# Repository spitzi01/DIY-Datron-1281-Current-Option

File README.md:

# DIY-Datron-1281-Current-Option
Add current measurement capabilities to your Datron 1281

I bought a defective Datron 1281. Sadly there was no option installed. So replicated the current measurement board as closely as I could. Most of the parts are still avaiable. The CLA3106 ASIC can be replaced with my CPLD replacement. The only problems are the JFETs for switching the low current ranges and the shunt resistors. The original JFETs were replaced with similar off-the-shelf ones. The shunt resistors are the most expensive part of this project, but there is no real other choice than Vishay foil resistors. Some resistors are custom ordered from Texas Components. The PCB features full mechanical compatibility to the original board and all guard traces.

I did some noise and linearity measurements with a DIY multifunction calibrator which uses a AD5791B and a ADR1000. The visible INL is due to the DAC INL. The noise of the 100mA range for example is 0,5µA pk2pk and 0,12µA rms. It is very possible that these measurements describe the performance of the calibrator. To know for sure, I would need a known current source.

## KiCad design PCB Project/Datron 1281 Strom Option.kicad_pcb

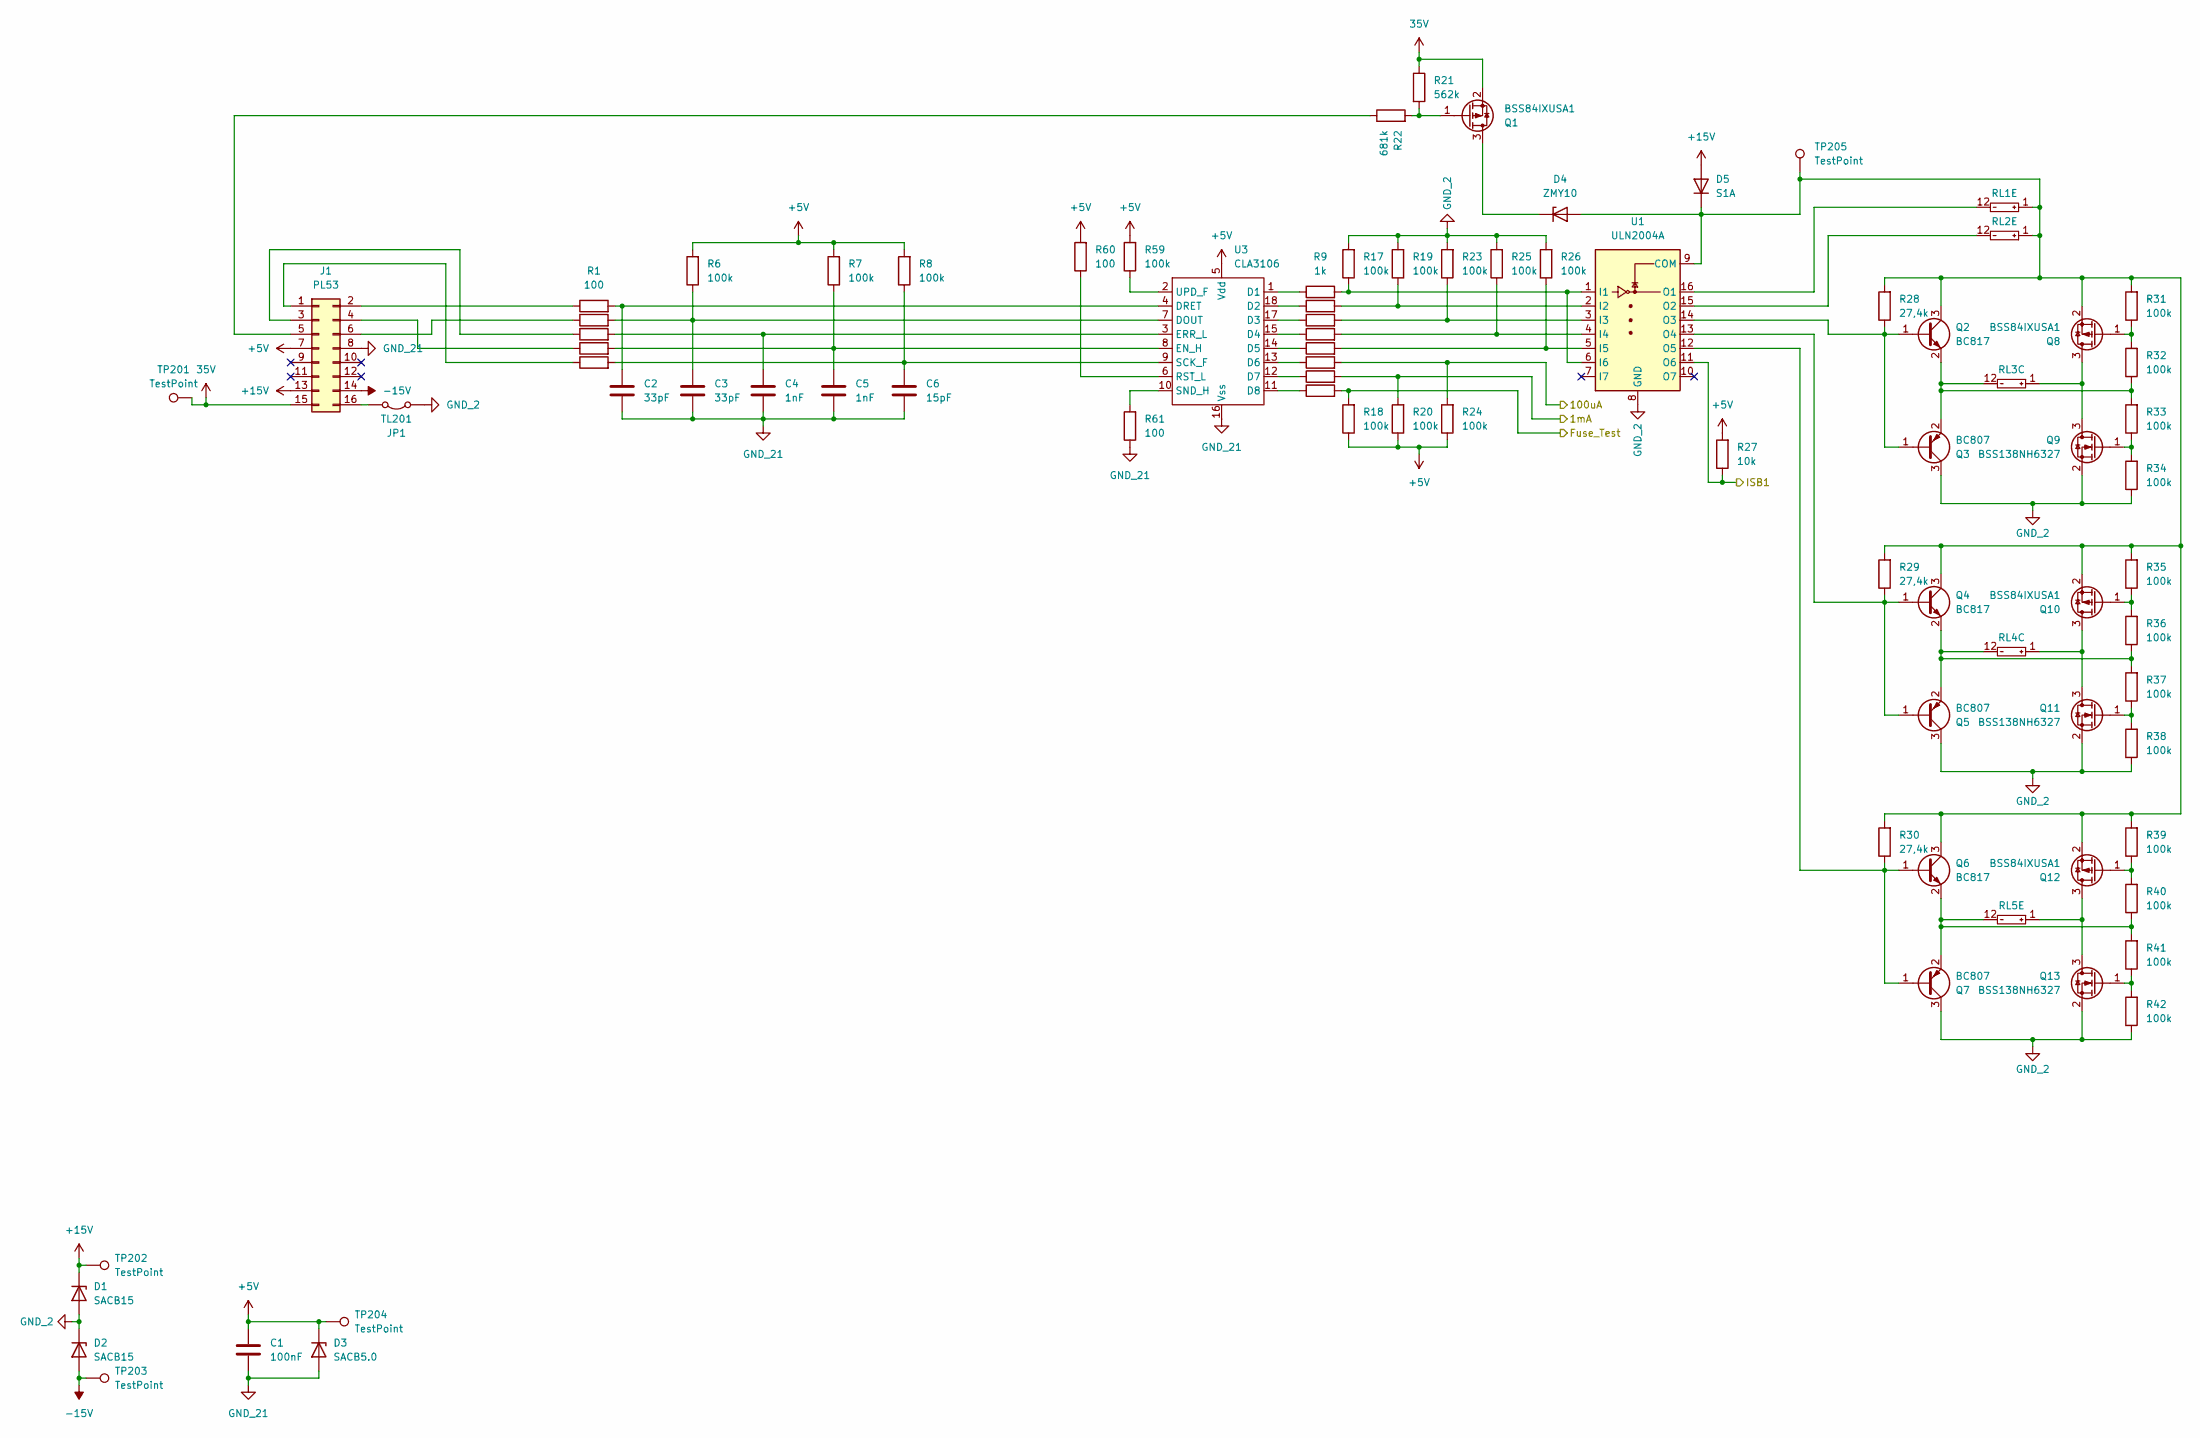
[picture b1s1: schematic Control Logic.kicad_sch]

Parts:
C1: 100nF; C_0805_2012Metric
C2, C3: 33pF; C_0805_2012Metric
C4, C5: 1nF; C_0805_2012Metric
C6: 15pF; C_0805_2012Metric
D1, D2: SACB15; D_SMB
D3: SACB5.0; D_SMB
D4: ZMY10; D_MELF
D5: S1A; D_SMA
J1: PL53; IDC-Header_2x08_P2.54mm_Vertical
JP1: TL201; TestPoint_2Pads_Pitch5.08mm_Drill1.3mm
Q1, Q8, Q10, Q12: BSS84IXUSA1; SOT-23-3
Q2, Q4, Q6: BC817; SOT-23
Q3, Q5, Q7: BC807; SOT-23
Q9, Q11, Q13: BSS138NH6327; SOT-23-3
R1, R2, R3, R4, R5, R60, R61: 100; R_0805_2012Metric
R6, R7, R8, R17, R18, R19, R20, R23, R24, R25, R26, R31, R32, R33, R34, R35, R36, R37, R38, R39, R40, R41, R42, R59: 100k; R_0805_2012Metric
R9, R10, R11, R12, R13, R14, R15, R16: 1k; R_0805_2012Metric
R21: 562k; R_0805_2012Metric
R22: 681k; R_0805_2012Metric
R27: 10k; R_0805_2012Metric
R28, R29, R30: 27,4k; R_0805_2012Metric
RL1, RL5: S3-DC24V; S3DC24V; Manufacturer_Part_Number S3-DC24V
RL2: S2-DC24V; S3DC24V; Manufacturer_Part_Number S2-DC24V
RL3, RL4: TX2-24V; Mouser Part Number 769-TX2-24V
TP201, TP202, TP203, TP204, TP205: TestPoint; TestPoint_Loop_D2.50mm_Drill1.0mm
U1: ULN2004A; SOIC-16W_5.3x10.2mm_P1.27mm
U3: CLA3106; DIP-18_W7.62mm_LongPads

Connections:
35V: J1.15, Q1.2 (S), R21.1, TP201.1
+5V: C1.1, D3.1 (K), J1.7, R6.2, R7.2, R8.2, R18.1, R20.1, R24.1, R27.2, R59.2, R60.2, TP204.1, U3.5 (Vdd); also elsewhere on the board
+15V: D1.1 (K), D5.2 (A), J1.13, TP202.1; also elsewhere on the board
-15V: D2.2 (A), J1.14, TP203.1; also elsewhere on the board
/Control Logic/1mA: R15.2, R20.2; also elsewhere on the board
/Control Logic/100uA: R14.2, R24.2; also elsewhere on the board
/Control Logic/Fuse_Test: R16.2, R18.2; also elsewhere on the board
/Control Logic/ISB1: R27.1, U1.11 (O6); also elsewhere on the board
GND_2: D1.2 (A), D2.1 (K), JP1.1 (A), Q3.3 (C), Q5.3 (C), Q7.3 (C), Q9.2 (S), Q11.2 (S), Q13.2 (S), R17.2, R19.2, R23.2, R25.2, R26.2, R34.1, R38.1, R42.1, U1.8 (GND); also elsewhere on the board
GND_21: C1.2, C2.2, C3.2, C4.2, C5.2, C6.2, D3.2 (A), J1.8, R61.1, U3.16 (Vss); also elsewhere on the board
unnamed: D4.2 (A), D5.1 (K), Q2.3 (C), Q4.3 (C), Q6.3 (C), Q8.2 (S), Q10.2 (S), Q12.2 (S), R28.2, R29.2, R30.2, R31.2, R35.2, R39.2, RL1.1, RL2.1, TP205.1, U1.9 (COM)
unnamed: D4.1 (K), Q1.3 (D)
unnamed: J1.1, R5.1
unnamed: J1.2, R1.1
unnamed: J1.3, R3.1
unnamed: J1.4, R4.1
unnamed: J1.5, R22.1
unnamed: J1.6, R2.1
unnamed: J1.16, JP1.2 (B)
unnamed: Q1.1 (G), R21.2, R22.2
unnamed: Q2.1 (B), Q3.1 (B), R28.1, U1.14 (O3)
unnamed: Q2.2 (E), Q3.2 (E), R32.1, R33.2, RL3.12
unnamed: Q4.1 (B), Q5.1 (B), R29.1, U1.13 (O4)
unnamed: Q4.2 (E), Q5.2 (E), R36.1, R37.2, RL4.12
unnamed: Q6.1 (B), Q7.1 (B), R30.1, U1.12 (O5)
unnamed: Q6.2 (E), Q7.2 (E), R40.1, R41.2, RL5.12
unnamed: Q8.3 (D), Q9.3 (D), RL3.1
unnamed: Q8.1 (G), R31.1, R32.2
unnamed: Q9.1 (G), R33.1, R34.2
unnamed: Q10.3 (D), Q11.3 (D), RL4.1
unnamed: Q10.1 (G), R35.1, R36.2
unnamed: Q11.1 (G), R37.1, R38.2
unnamed: Q12.3 (D), Q13.3 (D), RL5.1
unnamed: Q12.1 (G), R39.1, R40.2
unnamed: Q13.1 (G), R41.1, R42.2
unnamed: R9.2, R17.1, U1.1 (I1), U1.6 (I6)
unnamed: R10.2, R19.1, U1.2 (I2)
unnamed: R11.2, R23.1, U1.3 (I3)
unnamed: R12.2, R25.1, U1.4 (I4)
unnamed: R13.2, R26.1, U1.5 (I5)
unnamed: RL1.12, U1.16 (O1)
unnamed: RL2.12, U1.15 (O2)
unnamed: R9.1, U3.1 (D1)
unnamed: R10.1, U3.18 (D2)
unnamed: R11.1, U3.17 (D3)
unnamed: R12.1, U3.15 (D4)
unnamed: R13.1, U3.14 (D5)
unnamed: R14.1, U3.13 (D6)
unnamed: R15.1, U3.12 (D7)
unnamed: R16.1, U3.11 (D8)
unnamed: C3.1, R2.2, R6.1, U3.7 (DOUT)
unnamed: C2.1, R1.2, U3.4 (DRET)
unnamed: C5.1, R4.2, R7.1, U3.8 (EN_H)
unnamed: C4.1, R3.2, U3.3 (ERR_L)
unnamed: R60.1, U3.6 (RST_L)
unnamed: C6.1, R5.2, R8.1, U3.9 (SCK_F)
unnamed: R61.2, U3.10 (SND_H)
unnamed: R59.1, U3.2 (UPD_F)

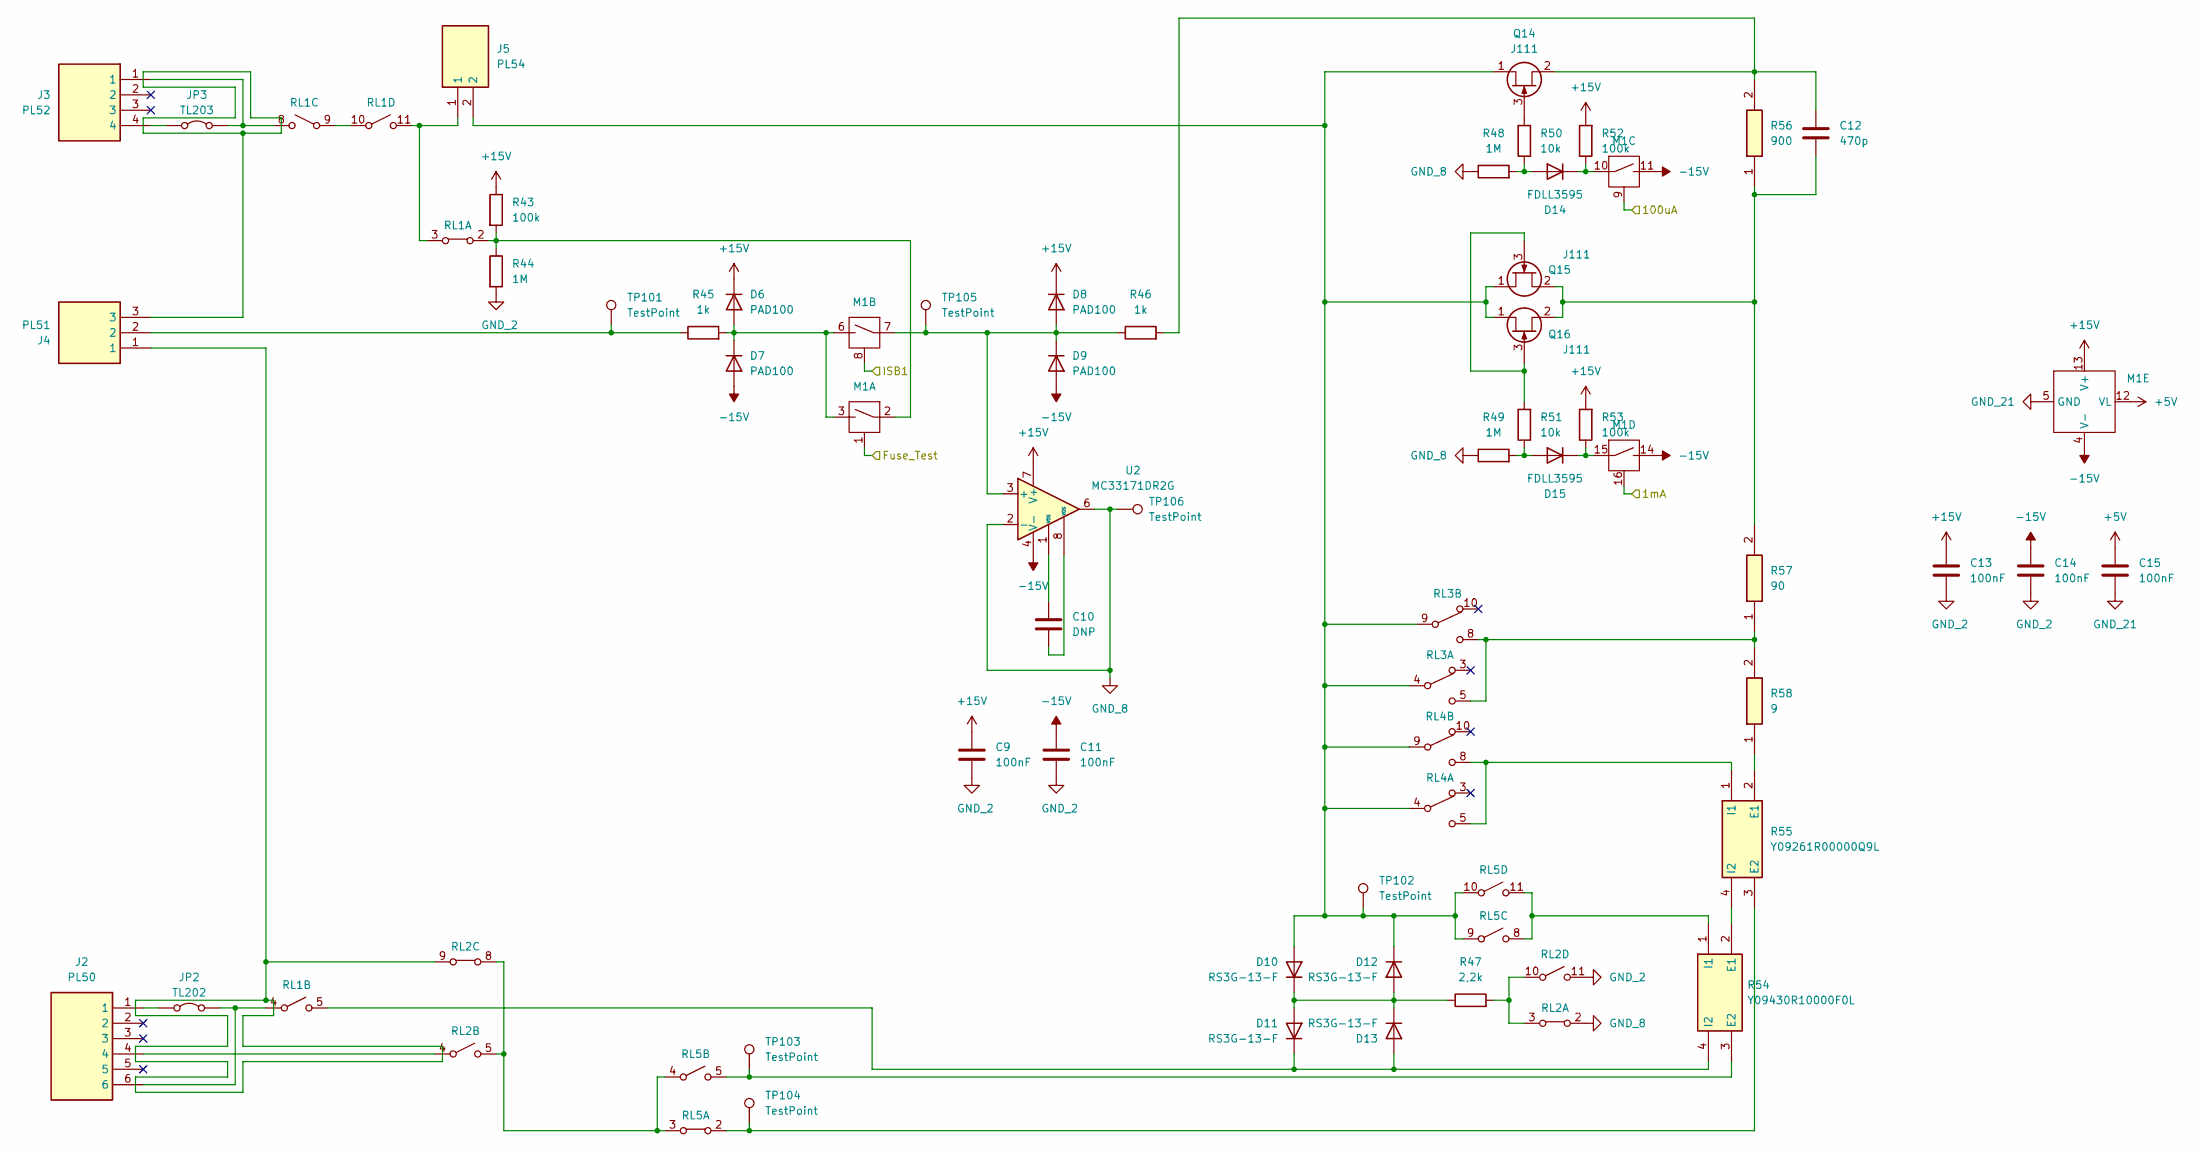
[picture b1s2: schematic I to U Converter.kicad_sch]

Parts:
C9, C11, C13, C14, C15: 100nF; C_0805_2012Metric
C10: DNP; C_0805_2012Metric
C12: 470p; C_0805_2012Metric
D6, D7, D8, D9: PAD100; TO-72-3
D10, D11, D12, D13: RS3G-13-F; D_SMC
D14, D15: FDLL3595; D_MiniMELF
J2: PL50; HDRV6W64P0X254_1X6_1524X580X1205P; Mouser Part Number 538-22-29-2061
J3: PL52; SHDR4W64P0X254_1X4_1016X580X1170P; Mouser Part Number 538-22-29-2041
J4: PL51; SHDR3W64P0X254_1X3_762X580X1170P; Mouser Part Number 538-22-29-2031
J5: PL54; SHDR2W64P0X254_1X2_508X580X1170P; Mouser Part Number 538-22-29-2021
JP2: TL202; TestPoint_2Pads_Pitch5.08mm_Drill1.3mm
JP3: TL203; TestPoint_2Pads_Pitch5.08mm_Drill1.3mm
M1: DG211BDY; SOIC127P600X175-16N; Mouser Part Number 781-DG211BDY-E3
Q14, Q15, Q16: J111; TO-92
R43, R52, R53: 100k; R_0805_2012Metric
R44, R48, R49: 1M; R_0805_2012Metric
R45, R46: 1k; R_0805_2012Metric
R47: 2,2k; R_0805_2012Metric
R50, R51: 10k; R_0805_2012Metric
R54: Y09430R10000F0L; Mouser Part Number 71-Y09430R10000F0L
R55: Y09261R00000Q9L; TO254P401X1016X2196-4P; Mouser Part Number N/A
R56: 900; Y145310K0000V9L; Manufacturer_Part_Number Y145310K0000V9L; Mouser Part Number N/A
R57: 90; Y145310K0000V9L; Manufacturer_Part_Number Y145310K0000V9L; Mouser Part Number N/A
R58: 9; Y145310K0000V9L; Manufacturer_Part_Number Y145310K0000V9L; Mouser Part Number N/A
RL1, RL5: S3-DC24V; S3DC24V; Manufacturer_Part_Number S3-DC24V
RL2: S2-DC24V; S3DC24V; Manufacturer_Part_Number S2-DC24V
RL3, RL4: TX2-24V; Mouser Part Number 769-TX2-24V
TP101, TP102, TP103, TP104, TP105, TP106: TestPoint; TestPoint_Loop_D2.50mm_Drill1.0mm
U2: MC33171DR2G; SOIC-8_3.9x4.9mm_P1.27mm

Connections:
+5V: C15.1, M1.12 (VL); also elsewhere on the board
+15V: C9.1, C13.1, D6.1 (K), D8.1 (K), M1.13 (V+), R43.1, R52.2, R53.2, U2.7 (V+); also elsewhere on the board
-15V: C11.1, C14.1, D7.2 (A), D9.2 (A), M1.4 (V-), M1.11, M1.14, U2.4 (V-); also elsewhere on the board
/Control Logic/1mA: M1.16; also elsewhere on the board
/Control Logic/100uA: M1.9; also elsewhere on the board
/Control Logic/Fuse_Test: M1.1; also elsewhere on the board
/Control Logic/ISB1: M1.8; also elsewhere on the board
GND_2: C9.2, C11.2, C13.2, C14.2, R44.2, RL2.11; also elsewhere on the board
GND_8: R48.1, R49.1, RL2.2, TP106.1, U2.2 (-), U2.6
GND_21: C15.2, M1.5 (GND); also elsewhere on the board
unnamed: C10.1, U2.1 (VOS)
unnamed: C10.2, U2.8 (VOS)
unnamed: D6.2 (A), D7.1 (K), M1.3, M1.6, R45.2
unnamed: D8.2 (A), D9.1 (K), M1.7, R46.1, TP105.1, U2.3 (+)
unnamed: D10.2 (A), D12.1 (K), J5.2, Q14.1 (D), Q15.1 (D), Q16.1 (D), RL3.4, RL3.9, RL4.4, RL4.9, RL5.9, RL5.10, TP102.1
unnamed: D10.1 (K), D11.2 (A), D12.2 (A), D13.1 (K), R47.1
unnamed: D11.1 (K), D13.2 (A), R54.4 (I2), RL1.5
unnamed: D14.2 (A), R48.2, R50.1
unnamed: D14.1 (K), M1.10, R52.1
unnamed: D15.2 (A), R49.2, R51.1
unnamed: D15.1 (K), M1.15, R53.1
unnamed: J2.4, RL2.4
unnamed: J4.1, RL2.9
unnamed: J4.2, R45.1, TP101.1
unnamed: J5.1, RL1.3, RL1.11
unnamed: J2.6, JP2.1 (A), RL1.4
unnamed: J2.1, JP2.2 (B)
unnamed: J3.1, JP3.1 (A), RL1.8
unnamed: J3.4, JP3.2 (B)
unnamed: M1.2, R43.2, R44.1, RL1.2
unnamed: Q14.3 (G), R50.2
unnamed: C12.1, Q14.2 (S), R46.2, R56.2
unnamed: Q15.3 (G), Q16.3 (G), R51.2
unnamed: C12.2, Q15.2 (S), Q16.2 (S), R56.1, R57.2
unnamed: R47.2, RL2.3, RL2.10
unnamed: R54.2 (E1), R55.4 (I2)
unnamed: R54.3 (E2), RL5.5, TP103.1
unnamed: R54.1 (I1), RL5.8, RL5.11
unnamed: R55.2 (E1), R58.1
unnamed: R55.3 (E2), RL5.2, TP104.1
unnamed: R55.1 (I1), RL4.5, RL4.8
unnamed: R57.1, R58.2, RL3.5, RL3.8
unnamed: RL1.9, RL1.10
unnamed: RL2.5, RL2.8, RL5.3, RL5.4

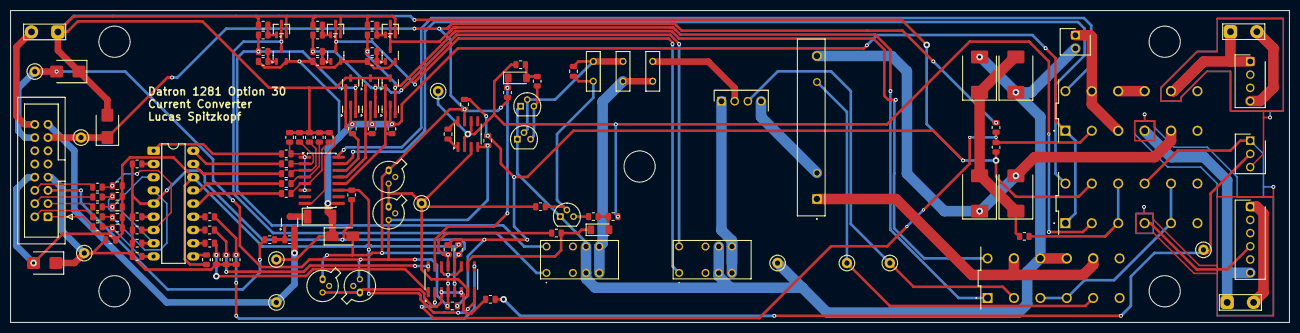
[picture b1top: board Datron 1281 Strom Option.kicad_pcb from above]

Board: 2 copper layers, 246.0 x 60.0 mm, 133 parts (0 on the bottom side), 93 nets.

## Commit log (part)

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2026-05-21 Add files via upload
    Corrected Footprint Library
